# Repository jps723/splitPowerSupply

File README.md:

# 12V Split Power Supply

For prototyping +/- 12v synthesizer modules, as seen in Kristian Blåsol's ['Modular in a Week'](https://www.youtube.com/watch?v=5DKU1m5_b_8) series on Youtube.

[12V/1a **AC** Power Supply](https://www.jameco.com/webapp/wcs/stores/servlet/ProductDisplay?catalogId=10001&langId=-1&storeId=10001&productId=100167) from Jameco.

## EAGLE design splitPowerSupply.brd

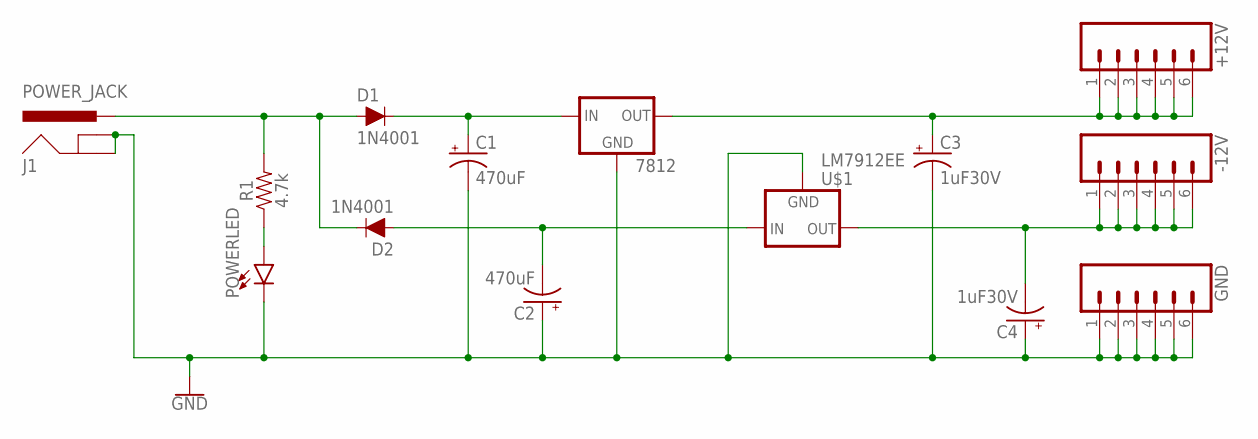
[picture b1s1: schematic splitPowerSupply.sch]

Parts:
7812: V_REG_78XX-TO-220; TO-220-ALT
+12V: CONN_06LONGPADS; 1X06_LONGPADS
-12V: CONN_06LONGPADS; 1X06_LONGPADS
C1, C2: 470uF; CPOL-RADIAL-2.5MM-5MM
C3, C4: 1uF30V; CPOL-RADIAL-2.5MM-5MM
D1, D2: 1N4001; DIODE-1N4001
GND: CONN_06LONGPADS; 1X06_LONGPADS
J1: POWER_JACK; POWER_JACK_PTH
POWERLED: LED-3MM-NO_SILK; LED_3MM-NS
R1: 4.7k; AXIAL-0.3
U$1: LM7912EE; 79XXL

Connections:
GND: 7812.GND, C1.2 (-), C2.1 (+), C3.2 (-), C4.1 (+), GND.1, GND.2, GND.3, GND.4, GND.5, GND.6, J1.GND, J1.GNDBREAK, POWERLED.K (C), U$1.GND
unnamed: D1.A, D2.C, J1.PWR, R1.P$2 (2)
unnamed: POWERLED.A, R1.P$1 (1)
unnamed: C2.2 (-), D2.A, U$1.IN
unnamed: 7812.IN, C1.1 (+), D1.C
unnamed: 7812.OUT, +12V.1, +12V.2, +12V.3, +12V.4, +12V.5, +12V.6, C3.1 (+)
unnamed: -12V.1, -12V.2, -12V.3, -12V.4, -12V.5, -12V.6, C4.2 (-), U$1.OUT

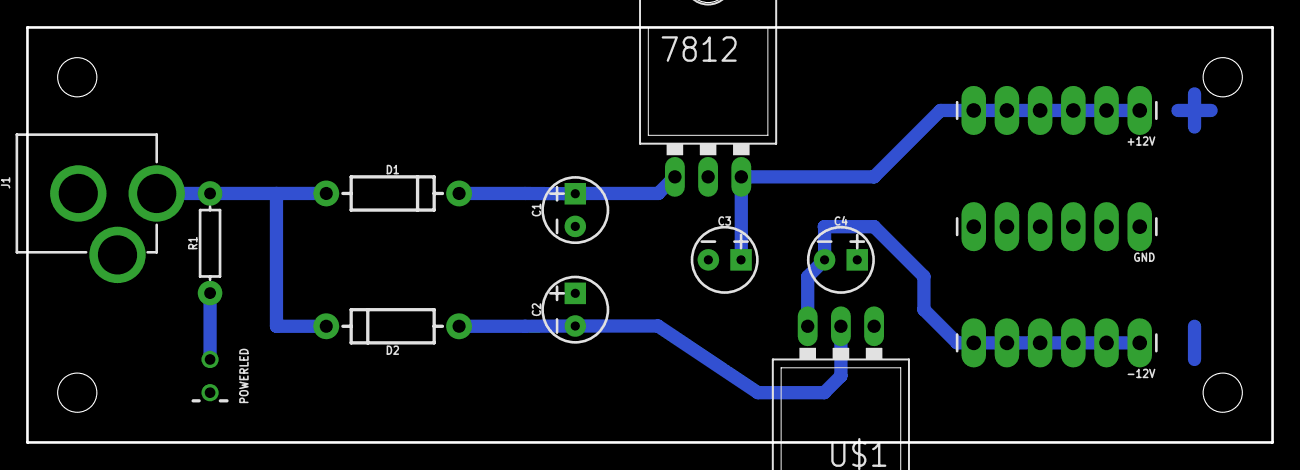
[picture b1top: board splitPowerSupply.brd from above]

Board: 2 copper layers, 95.2 x 31.7 mm, 14 parts (0 on the bottom side), 7 nets.

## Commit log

2020-10-29 added image to README
2020-10-29 Fixed image path
2020-11-15 updated readme with links and credit

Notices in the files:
parts and their libraries:
SparkFun-Capacitors: Licensing: Creative Commons ShareAlike 4.0 International - https://creativecommons.org/licenses/by-sa/4.0
